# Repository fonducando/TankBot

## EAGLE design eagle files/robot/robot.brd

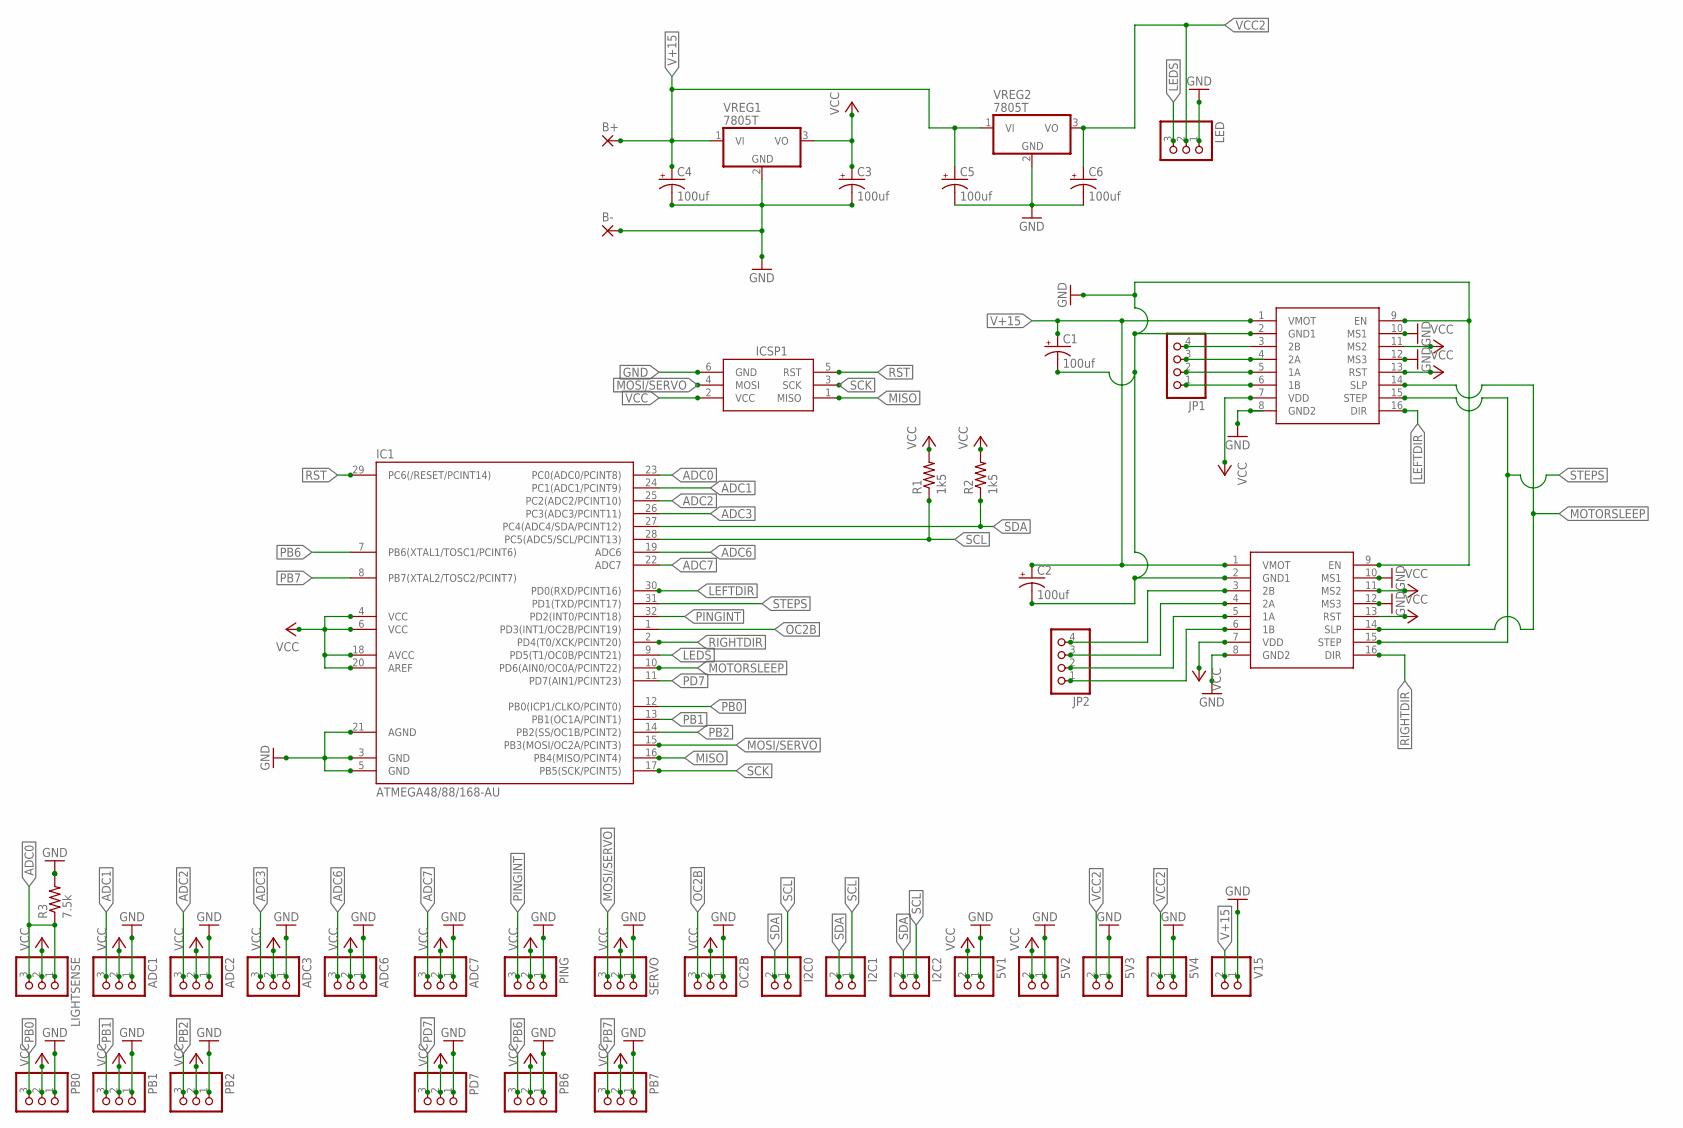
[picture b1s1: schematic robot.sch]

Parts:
5V1, 5V2, 5V3, 5V4: PINHD-1X2; 1X02
ADC1, ADC2, ADC3, ADC6, ADC7: PINHD-1X3; 1X03
B+: 3,81/1,4
B-: 3,81/1,4
C1, C2, C3, C4, C5, C6: 100uf; E3,5-8
I2C0, I2C1, I2C2: PINHD-1X2; 1X02
IC1: ATMEGA48/88/168-AU; TQFP32-08
ICSP1: AVRISP-6; AVRISP
JP1, JP2: PINHD-1X4; 1X04
LED: PINHD-1X3; 1X03
LEFTSTEPPER: POLOLUESTEPPERDRIVER; DIL16
LIGHTSENSE: PINHD-1X3; 1X03
OC2B: PINHD-1X3; 1X03
PB0, PB1, PB2, PB6, PB7: PINHD-1X3; 1X03
PD7: PINHD-1X3; 1X03
PING: PINHD-1X3; 1X03
R1, R2: 1k5; M1206
R3: 7.5k; 0309/10
RIGHTSTEPPER: POLOLUESTEPPERDRIVER; DIL16
SERVO: PINHD-1X3; 1X03
V15: PINHD-1X2; 1X02
VREG1, VREG2: 7805T; TO220H

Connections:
1-1A: JP1.2, LEFTSTEPPER.5 (1A)
1-1B: JP1.1, LEFTSTEPPER.6 (1B)
1-2A: JP1.3, LEFTSTEPPER.4 (2A)
1-2B: JP1.4, LEFTSTEPPER.3 (2B)
2-1A: JP2.2, RIGHTSTEPPER.5 (1A)
2-1B: JP2.1, RIGHTSTEPPER.6 (1B)
2-2A: JP2.3, RIGHTSTEPPER.4 (2A)
2-2B: JP2.4, RIGHTSTEPPER.3 (2B)
ADC0: IC1.23 (PC0(ADC0/PCINT8)), LIGHTSENSE.1, LIGHTSENSE.3, R3.1
ADC1: ADC1.3, IC1.24 (PC1(ADC1/PCINT9))
ADC2: ADC2.3, IC1.25 (PC2(ADC2/PCINT10))
ADC3: ADC3.3, IC1.26 (PC3(ADC3/PCINT11))
ADC6: ADC6.3, IC1.19 (ADC6)
ADC7: ADC7.3, IC1.22 (ADC7)
GND: 5V1.1, 5V2.1, 5V3.1, 5V4.1, ADC1.1, ADC2.1, ADC3.1, ADC6.1, ADC7.1, B-.1, C1.-, C2.-, C3.-, C4.-, C5.-, C6.-, IC1.3 (GND), IC1.5 (GND), IC1.21 (AGND), ICSP1.6 (GND), LED.1, LEFTSTEPPER.2 (GND1), LEFTSTEPPER.8 (GND2), LEFTSTEPPER.9 (EN), LEFTSTEPPER.10 (MS1), LEFTSTEPPER.12 (MS3), OC2B.1, PB0.1, PB1.1, PB2.1, PB6.1, PB7.1, PD7.1, PING.1, R3.2, RIGHTSTEPPER.2 (GND1), RIGHTSTEPPER.8 (GND2), RIGHTSTEPPER.9 (EN), RIGHTSTEPPER.10 (MS1), RIGHTSTEPPER.12 (MS3), SERVO.1, V15.1, VREG1.2 (GND), VREG2.2 (GND)
LEDS: IC1.9 (PD5(T1/OC0B/PCINT21)), LED.3
LEFTDIR: IC1.30 (PD0(RXD/PCINT16)), LEFTSTEPPER.16 (DIR)
MISO: IC1.16 (PB4(MISO/PCINT4)), ICSP1.1 (MISO)
MOSI/SERVO: IC1.15 (PB3(MOSI/OC2A/PCINT3)), ICSP1.4 (MOSI), SERVO.3
MOTORSLEEP: IC1.10 (PD6(AIN0/OC0A/PCINT22)), LEFTSTEPPER.14 (SLP), RIGHTSTEPPER.14 (SLP)
OC2B: IC1.1 (PD3(INT1/OC2B/PCINT19)), OC2B.3
PB0: IC1.12 (PB0(ICP1/CLKO/PCINT0)), PB0.3
PB1: IC1.13 (PB1(OC1A/PCINT1)), PB1.3
PB2: IC1.14 (PB2(SS/OC1B/PCINT2)), PB2.3
PB6: IC1.7 (PB6(XTAL1/TOSC1/PCINT6)), PB6.3
PB7: IC1.8 (PB7(XTAL2/TOSC2/PCINT7)), PB7.3
PD7: IC1.11 (PD7(AIN1/PCINT23)), PD7.3
PINGINT: IC1.32 (PD2(INT0/PCINT18)), PING.3
RIGHTDIR: IC1.2 (PD4(T0/XCK/PCINT20)), RIGHTSTEPPER.16 (DIR)
RST: IC1.29 (PC6(/RESET/PCINT14)), ICSP1.5 (RST)
SCK: IC1.17 (PB5(SCK/PCINT5)), ICSP1.3 (SCK)
SCL: I2C0.1, I2C1.1, I2C2.1, IC1.28 (PC5(ADC5/SCL/PCINT13)), R1.1
SDA: I2C0.2, I2C1.2, I2C2.2, IC1.27 (PC4(ADC4/SDA/PCINT12)), R2.1
STEPS: IC1.31 (PD1(TXD/PCINT17)), LEFTSTEPPER.15 (STEP), RIGHTSTEPPER.15 (STEP)
V+15: B+.1, C1.+, C2.+, C4.+, C5.+, LEFTSTEPPER.1 (VMOT), RIGHTSTEPPER.1 (VMOT), V15.2, VREG1.1 (VI), VREG2.1 (VI)
VCC: 5V1.2, 5V2.2, ADC1.2, ADC2.2, ADC3.2, ADC6.2, ADC7.2, C3.+, IC1.4 (VCC), IC1.6 (VCC), IC1.18 (AVCC), IC1.20 (AREF), ICSP1.2 (VCC), LEFTSTEPPER.7 (VDD), LEFTSTEPPER.11 (MS2), LEFTSTEPPER.13 (RST), LIGHTSENSE.2, OC2B.2, PB0.2, PB1.2, PB2.2, PB6.2, PB7.2, PD7.2, PING.2, R1.2, R2.2, RIGHTSTEPPER.7 (VDD), RIGHTSTEPPER.11 (MS2), RIGHTSTEPPER.13 (RST), SERVO.2, VREG1.3 (VO)
VCC2: 5V3.2, 5V4.2, C6.+, LED.2, VREG2.3 (VO)

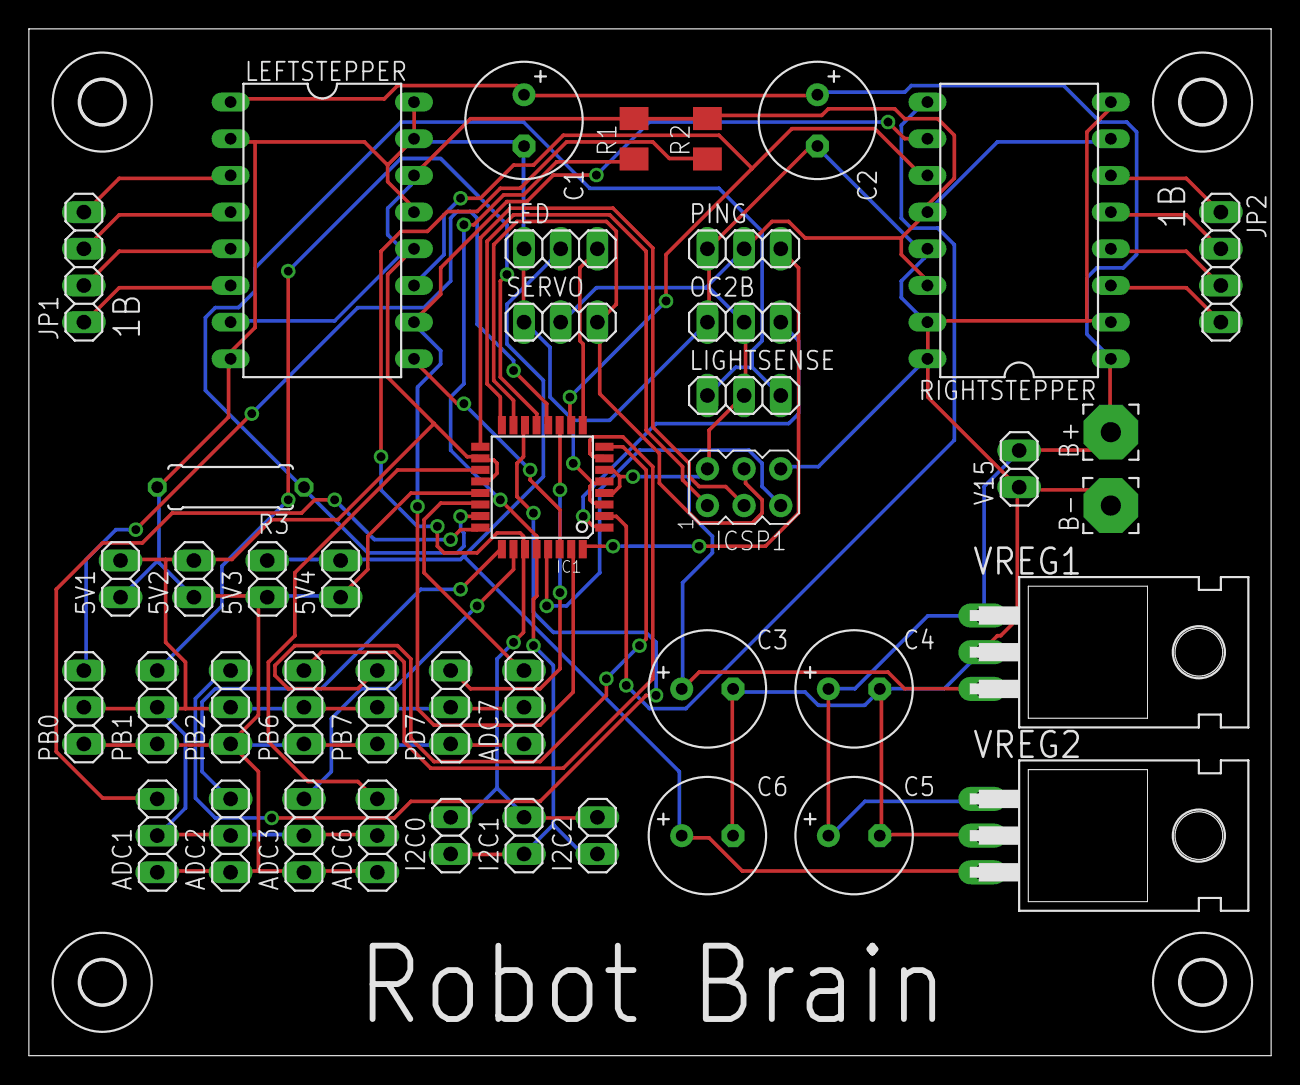
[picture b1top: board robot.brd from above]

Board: 2 copper layers, 86.0 x 71.1 mm, 47 parts (0 on the bottom side), 37 nets.

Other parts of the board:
U$1, U$2, U$3, U$4: 3,0

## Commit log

2019-12-08 Initial
    Initial
2019-12-08 Updated header in Main.cpp
